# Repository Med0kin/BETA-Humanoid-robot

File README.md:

## Table of content

- [Humanoid robot *BETA*](#humanoid-robot-beta)
- [Built with](#built-with)
  - [Hardware components](#hardware-components)
  - [Programming language](#programming-language)
  - [Used libraries](#used-libraries)
- [Construction](#construction)
- [Power supply](#power-supply)
- [Servo control](#servo-control)
  - [Disclaimer](#disclaimer)
  - [Pulse Servo](#pulse-servo)
  - [Bus Servo](#bus-servo)
  - [Sequencial movement](#sequencial-movement)
- [Application](#application)
- [Speech-to-text](#speech-to-text)
- [Pose estimation](#pose-estimation)
- [Safety precautions](#safety-precautions)
- [Future plans](#future-plans)

## Humanoid robot *BETA*

BETA is an ambitious undertaking that seeks to develop a humanoid robot possessing a range of human-like capabilities, including the ability to walk, see, and communicate verbally.

Conceived in 2018, the project has undergone several transformations and upgrades over the years. Currently, it is being developed as part of the *"Koło Naukowe Humanoid"* student research circle. Updates on its progress and new features are regularly shared on the group's [Facebook page](https://www.facebook.com/KNHStyleOfficial).

## Built with

### Hardware components

- [Raspberry Pi 4 Model B](https://www.raspberrypi.com/products/raspberry-pi-4-model-b/)
- [Raspberry Pi display](https://www.dfrobot.com/product-1784.html)
- [Bus servos](https://en.ocservo.com/?post_type=products&page_id=16170)
- Pulse servos: [RDS3235-180](https://pl.aliexpress.com/item/32734965011.html?spm=a2g0o.order_list.order_list_main.173.29321c247JQ9SQ&gatewayAdapt=glo2pol) and [RDS3115-270](https://pl.aliexpress.com/item/32270225462.html?spm=a2g0o.order_list.order_list_main.172.29321c24tig7ZX&gatewayAdapt=glo2pol)
- USB Webcam

### Programming language

The programming language of choice for the project is Python. This decision was made because of its ease of use, large community, large number of libraries and frameworks and cross-platform compatilibity. Additionally, Python is a versatile language that can be used to develop a wide range of applications, including those that are used for the control of the robot's servos, the implementation of its vision system, and the development of its speech recognition capabilities.

### Used libraries

- [PySide2](https://pypi.org/project/PySide2/) - GUI toolkit used in [Application](#application)
- [Selenium](https://www.selenium.dev/) - automation of browser used in [Speech-to-text](#speech-to-text)
- [OpenCV](https://opencv.org/) - real-time computer vision used in [Pose estimation](#pose-estimation)
- [OCServo](https://github.com/Shinnken/OCServo_App/) - servo control app used in [Servo control](#servo-control)
- [pigpio](https://pypi.org/project/pigpio/) - control of GPIO to generate software PWM signal to control [Pulse servos](#disclaimer).

## Construction

The framework of the robot is composed of a hybrid of components that are either 3D-printed, purchased, or self-fabricated. The design of these parts was created in Blender, a 3D modeling software, and subsequently constructed by our team.

Additionally, a 3D printer was utilized to produce the robot's chest component.

## Power supply

Humanoid robot BETA is powered by a combination of two step-up voltage regulators that convert 5V to 6V and 5V to 12V respectively. While this power supply configuration is functional, it is not an ideal solution for providing power to the robot's components.

## Servo control

As previously stated, our project utilizes two distinct types of servos. Due to their differing control mechanisms, we have partitioned their descriptions into two distinct subcategories.

### Disclaimer

Our use of the term "pulse" refers to a conventional servo that employs a Pulse Width Modulation (PWM) signal as its control input.

### Pulse Servo

Using mentioned library we've created tool to control servos with single commands.
To affix the servos to the robot's framework, we employ brackets that are included in the kit alongside the servos. The Raspberry Pi's GPIO pins serve as the source of the PWM signal, which is generated by utilizing the software [pigpio library](https://pypi.org/project/pigpio/). We have developed a tool utilizing the aforementioned library, which allows for the control of the servos through the use of single commands.

During the process of developing the robot, it became apparent that the existing servos were not ideally suited to our requirements, as they were prone to excessive play and struggled to maintain a fixed position. As a result, we made the decision to incorporate [Bus servos](#bus-servo) in the leg joints, as these offer superior stability and control. By leveraging this approach, we can enhance the overall performance and reliability of the system, while enabling greater precision and accuracy in its movements.

### Bus Servo

In regards to the management of the second group of servos, communication is established through the utilization of the UART protocol, as the servos in question incorporate internal electronics. This approach enables efficient transmission of commands and data, as well as simplifying the wiring and control of the servos. By interfacing with the internal electronics of the servos, the system can achieve greater precision and flexibility in its movements.

For more information about Bus servo control check out our [Servo library](https://github.com/Shinnken/OCServo_App/).

### Sequencial movement

To achieve smooth movement of our robot, we have developed a tool that enables the sequential control of servos. The primary objective of this tool is to facilitate the coordinated movement of servos to achieve seamless motion.

The program operates by utilizing text files, which contain data regarding the angles of each servo required for a given pose. By compiling a list of various poses, complex movements can be achieved through the sequential execution of poses. To create these text files, we have developed a custom tool that allows for the adjustment of the robot to a desired pose and the subsequent saving of this pose to a text file for later use.

## Application

The software application that has been developed utilizes the PySide2 library to create a graphical user interface (GUI). The primary objective of this application is to enable the user to manage and manipulate the behavior of a robot through a touch screen interface.

## Speech-to-text

For the purpose of speech-to-text, we have utilized the speech to textV website. The website is accessed through the use of the Selenium library. The library allows for the automation of the browser, which enables the implementation of the speech-to-text functionality.

One possible solution to address this issue is to utilize an application programming interface (API) that provides speech-to-text functionality. However, after careful consideration, it was determined that this approach was not optimal due to cost implications and implementation complexity. As an alternative, a solution was chosen that is both cost-effective and easy to implement, and does not impose excessive demands on computer resources.

## Pose estimation

For the purpose of pose estimation, the project team has chosen to use ArUco trackers, which are part of the OpenCV library. This is because ArUco markers are an efficient and accurate type of fiducial marker that can be easily detected and identified in image or video streams. By attaching multiple ArUco markers to the robot's limbs and joints, the position and orientation of these markers can be tracked to estimate the robot's pose with a high degree of accuracy.

In order to collect information about the location and orientation of the human body's joints and calculate angles for the robot, ArUco trackers will be attached to the human body. At this time, no other solutions have been selected for pose estimation purposes.

## Safety precautions

While operating humanoid robot BETA, it is important to take the necessary safety precautions to prevent injury or damage to the robot or its surroundings. Please read the following guidelines carefully before using the robot:

- Supervision: Always supervise the robot when it is in use. Do not leave the robot unattended around small children or pets.

- Operating environment: Use the robot in a safe and controlled environment. Avoid using the robot near stairs, ledges, or other hazards that could cause the robot to fall or be damaged.

- Power source: Only use the power source specified in the documentation. Do not use unauthorized power sources or chargers, as this could damage the robot or cause a fire.

- Servo control: When controlling the robot's servos, be aware of their range of motion and potential speed. Do not exceed the recommended range or speed, as this could damage the robot or cause it to malfunction.

- Maintenance: Regularly inspect the robot for wear and tear such as loose screws, frayed wires, or damaged components. If any issues are found, take the necessary steps to repair or replace the affected parts.

- Transport: When transporting the robot, make sure it is securely fastened and protected from damage.

By following these safety precautions, you can help ensure the safe and reliable operation of your humanoid robot BETA.

## Future plans

- [Power supply](#power-supply)

We plan to upgrade the power supply to a more efficient and stable configuration that uses step-down voltage regulators to convert 12V to 5V and 12V to 6V respectively.

The proposed power supply solution involves the use of a 3-cell lithium-ion battery.

By using a step-down voltage regulator to convert the 12V output from the battery to 5V and 6V respectively, we can ensure a stable and efficient power supply for the robot's components. This power supply solution also provides the added benefit of making the robot battery-powered, which increases its mobility and versatility.

We are confident that this proposed power supply solution will provide a safe, efficient, and reliable source of power for Humanoid robot BETA, and we look forward to implementing this upgrade in the near future.

- [Servo control](#servo-control)

As part of our future development plans, we intend to upgrade the current servos with more powerful alternatives. This enhancement will enable the creation of more intricate and sophisticated movements. In addition, we plan to incorporate a more advanced control system, which will allow for the implementation of more complex behaviors and actions.

- [Pose estimation](#pose-estimation)

The project team is considering adding gyroscope sensors to provide a more accurate source of information for angle estimation, thus allowing the robot to replicate human movements more accurately. Furthermore, a combination of different solutions, such as ArUco trackers, 2D pose estimation, and gyroscopes, may be tested to determine which approach yields the best results.

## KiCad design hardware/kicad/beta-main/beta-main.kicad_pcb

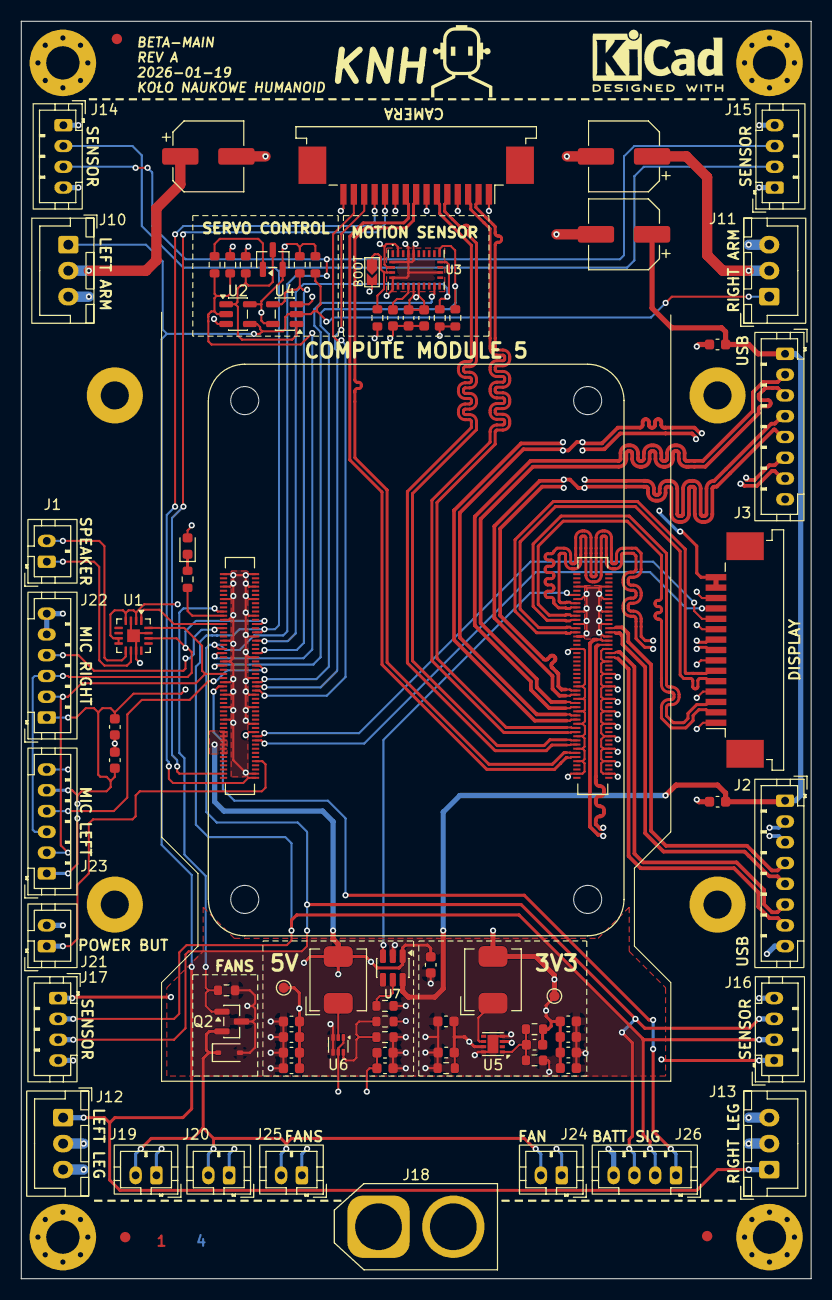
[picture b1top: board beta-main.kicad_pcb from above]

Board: 4 copper layers, 76.0 x 121.0 mm, 90 parts (0 on the bottom side), 66 nets.

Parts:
C1, C22, C23: 0.1u; C_0603_1608Metric
C2, C12, C24: 100u; CP_Elec_6.3x5.7
C3, C4, C5, C6, C7, C8, C9, C11, C13, C14, C15, C16, C17, C18, C19, C20, C21: 10u; C_0603_1608Metric
C10: 4.7nF; C_0603_1608Metric
CM5: ComputeModule5-CM5; Raspberry-Pi-5-Compute-Module
D1: LED_RED; LED_0603_1608Metric
D2: 1N5819WS; D_SOD-323
FID1, FID2, FID3: Fiducial_1mm_Mask2mm
J1, J19, J20, J21, J24, J25: Conn_01x02_Pin; JST_PH_B2B-PH-K_1x02_P2.00mm_Vertical
J2, J3: Conn_01x08_Pin; JST_PH_B8B-PH-K_1x08_P2.00mm_Vertical
J5, J8: FFC; TE_1-84953-5_1x15-1MP_P1.0mm_Horizontal
J10, J11, J12, J13: Conn_01x03_Pin; JST_XH_B3B-XH-A_1x03_P2.50mm_Vertical
J14, J15, J16, J17, J26: Conn_01x04_Pin; JST_PH_B4B-PH-K_1x04_P2.00mm_Vertical
J18: XT60; AMASS_XT60-F_1x02_P7.20mm_Vertical
J22, J23: Conn_01x06_Pin; JST_PH_B6B-PH-K_1x06_P2.00mm_Vertical
JP1: SolderJumper_2_Open; SolderJumper-2
L1, L2: 2.2u; L_Bourns_SRP5030CC
MH1, MH3, MH5, MH7: M3; MountingHole_3.2mm_M3_Pad_Via
MH9, MH10, MH11, MH12: M2.5; MountingHole_2.7mm_Pad
Q1: MMBT3906; SOT-23
Q2: IRLML6246TRP; SOT-23
R1: 20k; R_0603_1608Metric
R2, R3, R4, R5, R6, R13, R14, R15, R16: 10k; R_0603_1608Metric
R7: 220K; R_0603_1608Metric
R8: 30K; R_0603_1608Metric
R9: 15k; R_0603_1608Metric
R10: 10K 1%; R_0603_1608Metric
R11: 2.2K 1%; R_0603_1608Metric
R12: 100; R_0603_1608Metric
TP1: 5V; TestPoint_Pad_D1.0mm
TP2: 3V3; TestPoint_Pad_D1.0mm
U1: MAX98357A; TQFN-16-1EP_3x3mm_P0.5mm_EP1.23x1.23mm
U2, U4: 74LVC1G126; SOT-23-5
U3: BNO086; IC_BNO086
U5: AP3441SHE-7B; DFN-8-1EP_2x2mm_P0.5mm_EP1.05x1.75mm
U6: TPS56624x; SOT-563
U7: AP2553W6; SOT-23-6

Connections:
+3V3: C7.1, C8.1, C10.1, C13.1, C16.1, C18.1, C20.1, C22.1, C23.1, CM5.78 (GPIO_VREF(1.8v/3.3v_Input)), D1.2 (A), J5.14, J5.15, J8.15, J14.1, J15.1, J16.1, J17.1, J22.1, J23.1, J23.5, L2.2, Q1.2 (E), R3.1, R4.1, R5.1, R10.1, R14.1, R15.1, R16.1, TP2.1, U1.2 (GAIN_SLOT), U1.4 (~SD_MODE), U1.7 (VDD), U1.8 (VDD), U2.5 (VCC), U3.3 (VDD), U3.10 (CLKSEL0), U3.11 (~RST), U3.28 (VDDIO), U4.5 (VCC)
+5V: C4.1, C5.1, C9.1, C11.1, C14.1, C17.1, C19.1, CM5.77 (+5v_(Input)), CM5.79 (+5v_(Input)), CM5.81 (+5v_(Input)), CM5.83 (+5v_(Input)), CM5.85 (+5v_(Input)), CM5.87 (+5v_(Input)), L1.2, R6.1, R7.1, TP1.1, U5.3 (VIN), U5.7 (EN), U7.1 (IN)
+BATT: C2.1, C3.1, C6.1, C24.1, J10.2, J11.2, J12.2, J13.2, J18.2, J19.1, J20.1, J24.1, J25.1, U6.1 (VIN), U6.5 (EN)
/CAM_GPIO0: CM5.97 (CAM_GPIO0), J8.11
/CAM_GPIO1: CM5.100 (CAM_GPIO1), J8.12
/GPIO/BATT_INT: CM5.55 (GPIO14), J26.1
/GPIO/FAN_PWM: CM5.19 (FAN_PWM), Q2.1 (G), R13.1
/GPIO/I2C2_SCL: CM5.34 (GPIO5), R15.2, U3.19 (H_SCL/SCK/RX)
/GPIO/I2C2_SDA: CM5.54 (GPIO4), R16.2, U3.20 (H_SDA/H_MISO/TX)
/GPIO/PWR_BUT: CM5.92 (PWR_BUT), J21.1
/GPIO/SDI: CM5.45 (GPIO24), U3.14 (~H_INT)
/GPIO/UART3_RX: CM5.40 (GPIO9), R5.2, U4.4
/GPIO/UART3_TX: CM5.39 (GPIO8), R2.2, R3.2, U2.2
/High Speed Serial/USB3-0-D_N: CM5.136 (USB3-0-D_N), J2.2
/High Speed Serial/USB3-0-D_P: CM5.134 (USB3-0-D_P), J2.3
/High Speed Serial/USB3-0-RX_N: CM5.128 (USB3-0-RX_N), J2.4
/High Speed Serial/USB3-0-RX_P: CM5.130 (USB3-0-RX_P), J2.5
/High Speed Serial/USB3-0-TX_N: CM5.140 (USB3-0-TX_N), J2.6
/High Speed Serial/USB3-0-TX_P: CM5.142 (USB3-0-TX_P), J2.7
/High Speed Serial/USB3-1-D_N: CM5.165 (USB3-1-D_N), J3.2
/High Speed Serial/USB3-1-D_P: CM5.163 (USB3-1-D_P), J3.3
/High Speed Serial/USB3-1-RX_N: CM5.157 (USB3-1-RX_N), J3.4
/High Speed Serial/USB3-1-RX_P: CM5.159 (USB3-1-RX_P), J3.5
/High Speed Serial/USB3-1-TX_N: CM5.169 (USB3-1-TX_N), J3.6
/High Speed Serial/USB3-1-TX_P: CM5.171 (USB3-1-TX_P), J3.7
/I2S0_SCLK: CM5.49 (GPIO18), J22.2, J23.2, U1.16 (BCLK)
/I2S0_SDI0: CM5.27 (GPIO20), J22.4
/I2S0_SDI1: CM5.46 (GPIO22), J23.4
/I2S0_SDO: CM5.25 (GPIO21), U1.1 (DIN)
/I2S0_WS: CM5.26 (GPIO19), J22.3, J23.3, U1.14 (LRCLK)
/MIPI0_C_N: CM5.127 (MIPI0_C_N), J5.5
/MIPI0_C_P: CM5.129 (MIPI0_C_P), J5.6
/MIPI0_D0_N: CM5.115 (MIPI0_D0_N), J5.8
/MIPI0_D0_P: CM5.117 (MIPI0_D0_P), J5.9
/MIPI0_D1_N: CM5.121 (MIPI0_D1_N), J5.2
/MIPI0_D1_P: CM5.123 (MIPI0_D1_P), J5.3
/MIPI1_C_N: CM5.187 (MIPI1_C_N), J8.8
/MIPI1_C_P: CM5.189 (MIPI1_C_P), J8.9
/MIPI1_D0_N: CM5.175 (MIPI1_D0_N), J8.2
/MIPI1_D0_P: CM5.177 (MIPI1_D0_P), J8.3
/MIPI1_D1_N: CM5.181 (MIPI1_D1_N), J8.5
/MIPI1_D1_P: CM5.183 (MIPI1_D1_P), J8.6
/PSU/FB: C10.2, R10.2, R11.1, U5.1 (FB)
/Peripherals/SENSOR_SCL: CM5.37 (GPIO7), J14.3, J15.3, J16.3, J17.3, J26.3
/Peripherals/SENSOR_SDA: CM5.30 (GPIO6), J14.2, J15.2, J16.2, J17.2, J26.2
/Peripherals/SIG: J10.1, J11.1, J12.1, J13.1, R4.2, U2.4, U4.2
/Peripherals/TXEN: Q1.3 (C), R1.2, U2.1, U4.1
/SCL0: CM5.80 (SCL0), J5.11
/SCL1: CM5.56 (GPIO3), J8.13
/SDA0: CM5.82 (SDA0), J5.12
/SDA1: CM5.58 (GPIO2), J8.14
/VBUS_EN: CM5.111 (VBUS_EN), U7.3 (EN)
GND: C1.1, C2.2, C3.2, C4.2, C5.2, C6.2, C7.2, C8.2, C9.2, C11.2, C12.2, C13.2, C14.2, C15.2, C16.2, C17.2, C18.2, C19.2, C20.2, C21.2, C22.2, C23.2, C24.2, CM5.1 (GND), CM5.2 (GND), CM5.7 (GND), CM5.8 (GND), CM5.13 (GND), CM5.14 (GND), CM5.22 (GND), CM5.23 (GND), CM5.32 (GND), CM5.33 (GND), CM5.42 (GND), CM5.43 (GND), CM5.52 (GND), CM5.53 (GND), CM5.59 (GND), CM5.60 (GND), CM5.65 (GND), CM5.66 (GND), CM5.71 (GND), CM5.74 (GND), CM5.98 (GND), CM5.107 (GND), CM5.108 (GND), CM5.113 (GND), CM5.114 (GND), CM5.119 (GND), CM5.120 (GND), CM5.125 (GND), CM5.126 (GND), CM5.131 (GND), CM5.132 (GND), CM5.137 (GND), CM5.138 (GND), CM5.144 (GND), CM5.150 (GND), CM5.155 (GND), CM5.156 (GND), CM5.161 (GND), CM5.162 (GND), CM5.167 (GND), CM5.168 (GND), CM5.173 (GND), CM5.174 (GND), CM5.179 (GND), CM5.180 (GND), CM5.185 (GND), CM5.186 (GND), CM5.191 (GND), CM5.192 (GND), CM5.197 (GND), CM5.198 (GND), D2.2 (A), J2.8, J3.8, J5.1, J5.4, J5.7, J5.10, J5.13, J8.1, J8.4, J8.7, J8.10, J10.3, J11.3, J12.3, J13.3, J14.4, J15.4, J16.4, J17.4, J18.1, J21.2, J22.5, J22.6, J23.6, J26.4, JP1.2 (B), MH1.1, MH3.1, MH5.1, MH7.1, MH9.1, MH10.1, MH11.1, MH12.1, Q2.3 (S), R1.1, R6.2, R8.2, R9.2, R11.2, R13.2, U1.3 (GND), U1.11 (GND), U1.15 (GND), U1.17 (PAD), U2.3 (GND), U3.2 (GND), U3.5 (PS1), U3.6 (PS0/WAKE), U3.17 (SA0/H_MOSI), U3.25 (GNDIO), U3.26 (XOUT32/CLKSEL1), U4.3 (GND), U5.4 (PGND), U5.8 (SGND), U5.9 (PAD), U6.3 (GND), U6.4 (AGND), U7.2 (GND)
unnamed: CM5.21 (LED_nACT), R12.1
unnamed: D1.1 (K), R12.2
unnamed: D2.1 (K), J19.2, J20.2, J24.2, J25.2, Q2.2 (D)
unnamed: J1.1, U1.10 (OUTN)
unnamed: J1.2, U1.9 (OUTP)
unnamed: JP1.1 (A), R14.2, U3.4 (~BOOT)
unnamed: Q1.1 (B), R2.1
unnamed: C1.2, U3.9 (CAP)
unnamed: L2.1, U5.6 (LX)
unnamed: R7.2, R8.1, U6.6 (FB)
unnamed: L1.1, U6.2 (SW)
unnamed: R9.1, U7.5 (ILIM)
VBUS: C12.1, C15.1, C21.1, J2.1, J3.1, U7.6 (OUT)

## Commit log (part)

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2023-03-13 another fix
2023-03-13 10 seconds
2023-03-13 And another fix
2023-03-13 hopefully last selenium fix
2023-03-13 another one
2023-03-13 lets go
2023-03-13 New page test
2023-03-13 small fix
2023-03-13 Encoding fix
2023-03-13 almost done
2023-03-13 test
2023-03-13 next
2023-03-13 hopefully now
2023-03-13 Now it works
2023-03-14 Tidied code a bit, preparing test
2023-03-14 First test
2023-03-14 s2t lib changes + window app text
2023-03-14 fixed hiding labels
2023-03-14 s2t in windowapp
2023-03-14 s2t utf-8 fix
2023-03-14 change name
2023-03-14 no fullscreen
2023-03-14 start thread
2023-03-14 better threading
2023-03-14 text change
2023-03-14 text
2023-03-14 works?
2023-03-14 next test
2023-03-14 no idea how floor in python works
2023-03-14 Fu***** typo __int__ instead of __init__
2023-03-14 Auto run pigpiod
2023-03-14 later to fix
2023-03-14 Now we're talking
2023-03-14 Test loop
2023-03-14 minor fix
2023-03-14 more testing
2023-03-14 Full body test
2023-03-14 Forgot about transform again XD
2023-03-14 continue testing
2023-03-14 Success
2023-03-14 Test with sync
2023-03-14 Tuple test
2023-03-14 Another combo
2023-03-14 Revert back to better ideas
2023-03-14 Little patch
2023-03-14 Changed time
2023-03-14 servo arm control
2023-03-14 servo control
2023-03-14 set servo ranges
2023-03-14 servo settings
2023-03-14 left arm control
2023-03-14 Arms app update
2023-03-14 Arms app another update
2023-03-14 Next update
2023-03-14 Export pos test
2023-03-14 Export pos hopefully done
2023-03-14 Export pos fix
2023-03-14 preparing libs for window app
2023-03-14 Servo App import
2023-03-14 Servo App import fix
2023-03-14 added servo lib
2023-03-14 Servo added sequence
2023-03-14 adding reaction
2023-03-14 added reaction
2023-03-14 back to fullscreen
2023-03-14 fixedwith for textbox
2023-03-14 thread joining test
2023-03-14 better thread stopping?
2023-03-14 thread fix?
2023-03-14 react thread fix
2023-03-14 text label wordwrap
2023-03-14 better react
2023-03-14 fix - p3.7 has no match case
2023-03-14 encoding to utf8
2023-03-14 Test sequence
2023-03-14 organisation
2023-03-14 change lib
2023-03-14 dance sequence
2023-03-14 all positions
2023-03-14 Kicked transform from digital servo
2023-03-14 time correction
2023-03-14 Fixed servo order
2023-03-14 Time patch
2023-03-14 Servo rearrangement
2023-03-14 Small fixes
2023-03-14 Each time bit closer
2023-03-14 pose estim
2023-03-14 cgane import
2023-03-14 change impport
2023-03-14 turning off pe
2023-03-14 adding txts
2023-03-14 test pe
2023-03-14 New file
2023-03-14 Transferred positions to main directory
2023-03-14 added frame counter
2023-03-14 quiting browser
2023-03-14 fix frame counter
2023-03-14 Minor fixes
2023-03-14 fixed wrong naming
2023-03-14 Servo range fix
2023-03-14 squat and standing up
2023-03-14 Servo pos fix
2023-03-15 Walk
2023-03-15 dancing
2023-03-15 moves sequences
2023-03-15 Walking loop
2023-03-15 Dance and walk over voice test
2023-03-15 Acrobations in different thread
2023-03-15 Hopefuly robot now can dance
2023-03-15 Two steps instead of one
2023-03-15 walking with marker
2023-03-15 fixed buttons
2023-03-15 tostring
2023-03-15 good value
2023-03-15 dance fix
2023-03-22 update - still needs editing
2023-03-28 speed (dancing, arms)
2023-03-28 dance-speed corection
2023-03-28 dance (speed correction)
2023-03-28 dance (speed correction 2)
2023-03-28 dance (time sleep)
2023-03-28 dance (timing)
2023-03-28 dance-timing
2023-03-28 dance timing
2023-04-01 :green_heart: Moving txt files to subdirectory
2023-04-01 :bug: Fixing directory issue
2023-04-01 :sparkles: Server testing
2023-04-01 :construction: Server testing
2023-04-02 :memo: Updating README with new content
2023-04-02 :memo: fixing typo
2023-04-07 Update s2t_lib.py
    🐛 s2t_lib fix
2023-04-07 📝 Write README #3
2023-04-07 📝 Write README #3 update
2023-04-07 :memo: Fixing .gif file
2023-04-07 📝 Write README #3 Added new content
2023-04-07 :memo: Create LICENSE
2023-04-11 :recycle: Moving unnecessary files to subdirectory
2023-04-11 :memo: 📝 Write README #3 Added new content
2023-04-11 📝 Write README #3 Adding new content
2023-04-11 📝 Write README #3 New banner
2023-04-11 📝 Write README #3 Done
2023-04-11 :memo: Adding pdf version of README file
2023-04-12 :memo: Edit out readme file
2023-04-12 :sparkles: Added waving animation
2023-04-12 :bug: Fix for stt
2023-04-12 :bug: Fix for wave
2023-04-13 :memo: Adding readme file in polish language
2023-04-13 :memo: Fixing typos in readme file
2023-04-13 💬 Adding comments to the code
2023-04-13 💬 Add comments
2023-05-11 :construction: Testing
2023-05-11 :contruction: Testing
2023-05-11 :construction: Test
2023-05-11 :costruction: Test
2023-05-12 :construction: Del react loop and add Arm Control
2023-05-12 :wrench: Fix not assigned old text
2023-05-12 :contruction: Test resized app
2023-05-12 :contruction: Test
2023-05-30 :construction: Add changes (languages)
2023-05-31 :construction: Arm pos creator directory fix
2023-06-01 :construction: Add lang change
2023-06-01 :construction: Change lang names
2023-06-01 :construction: Add changes
2023-06-03 :construction: Add lang model
2023-06-03 :sparkles: Add new positions
2023-06-03 :construction: Added controllers
2023-06-03 :construction: Added music
2023-06-03 :red: delete controllers
2023-06-03 :construction: OCServo fix
2023-06-03 :sparkles: Add dances
2023-06-03 :construction: add dances
2023-06-03 :construction: fix dances
2023-06-03 :construction: speed fix
2023-06-04 dance time fix
2023-06-04 music vol.2
2023-06-04 :construction: Add new chatbot model
2023-06-04 fdas
2023-06-04 music vol. 3
2023-06-04 :construction: ballerina fix
2023-06-04 turning fix
2023-06-04 music (ballerina, twist, jogging)
2023-06-04 add new call
2023-06-04 music (hiphop)
2023-06-04 dsadas
2023-06-04 walk fix
2023-06-04 commi msg
2023-06-04 window
2023-06-04 change
2023-06-04 buttons
2023-06-04 sfgfg
2023-06-04 dthsdthdth
2023-06-04 fdsa
2023-06-04 adss
2023-06-30 :wrench: Add gitignore to prevent bytecode upload
2023-07-16 folder Positions_dict added
2023-10-09 ballerina fix
2023-10-09 enable ballerina dance
2023-10-09 test3 - dodanie na koncu setsequence
2023-10-09 test4
2023-10-09 disable fullscreen
2023-10-09 fix prionting
2023-10-09 final?
2023-10-10 last final pls?
2023-10-10 working listening and extected reactions
2023-10-10 add fullscreen
2023-10-10 Change of jogging2 music file
2023-10-17 Adding optimized code
2023-10-17 Add test for PWMServo
2023-10-17 Fix test model paths
2023-10-17 Fix name conflict
2023-10-17 Troubleshooting
2023-10-19 Fix wrong README dir
2023-10-29 Add ServoController test and new features
2024-12-06 :construction: Cleanup
2024-12-07 refactor
2024-12-08 Init
2025-01-06 Enhance GUI and model structure with new components and fixes
    - Added QAnimatedPixmapItem for animated graphics in the GUI.
    - Updated import paths for consistency across modules.
    - Improved Servo class with is_inverted property for better control.
    - Introduced Model class to manage servo instances and serial communication.
    - Fixed minor syntax issues and improved code readability.
    - Added initial test for BusServo functionality.
2025-05-25 Big update after changing hip width
2025-05-25 Cleanup
2025-10-16 add kicad main board project
2025-10-16 tweaks and added servo controller
2025-10-16 tweaks
2025-10-17 add 5v power supply
2025-10-26 sync changes after meeting
2025-10-29 Wzmacniacz dodany
2025-11-02 Dodanie schematu sekcji zasilania 3V3
2025-11-08 New test for TTS engine based on huggingface resouces.
2025-11-08 new sox for test
2025-12-11 5V and amplifier corrections
2025-12-16 Amplifier set for left channel only and god rid of all errors from ERC
2025-12-18 Gyroscope added without errors in ERC
2025-12-20 Setup for PCB layout
2025-12-22 remove power symbols from hierarchy and move different subsystems around
2025-12-22 use copied MAX98357 symbol to specify pin type
2025-12-23 BNO086 tweaked
2025-12-23 create template for components placement with drawn contraints
2025-12-27 Rough layout with all elements, test point for 3V3 added. C footprints need to change to 6 3
2025-12-27 Datasheets added, camera and servo not included
2026-01-04 Footprints changed to 603
2026-01-04 Footprints fixed, fuse removed
2026-01-05 add modifications
2026-01-05 add filled zones and layout 5V and 3V3
2026-01-05 add fan control
2026-01-05 route servo controller
2026-01-09 route usb
2026-01-09 BOM passive
2026-01-09 sync
2026-01-10 BOM, all easily found parts from digi
2026-01-12 resolve DRC issues and generate fab files
2026-01-13 sync changes
2026-01-19 add final touches, generate rev A fab and step files
2026-01-20 regenerate fab files
